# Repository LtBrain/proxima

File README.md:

# proxima
A TVC and fin control flight computer

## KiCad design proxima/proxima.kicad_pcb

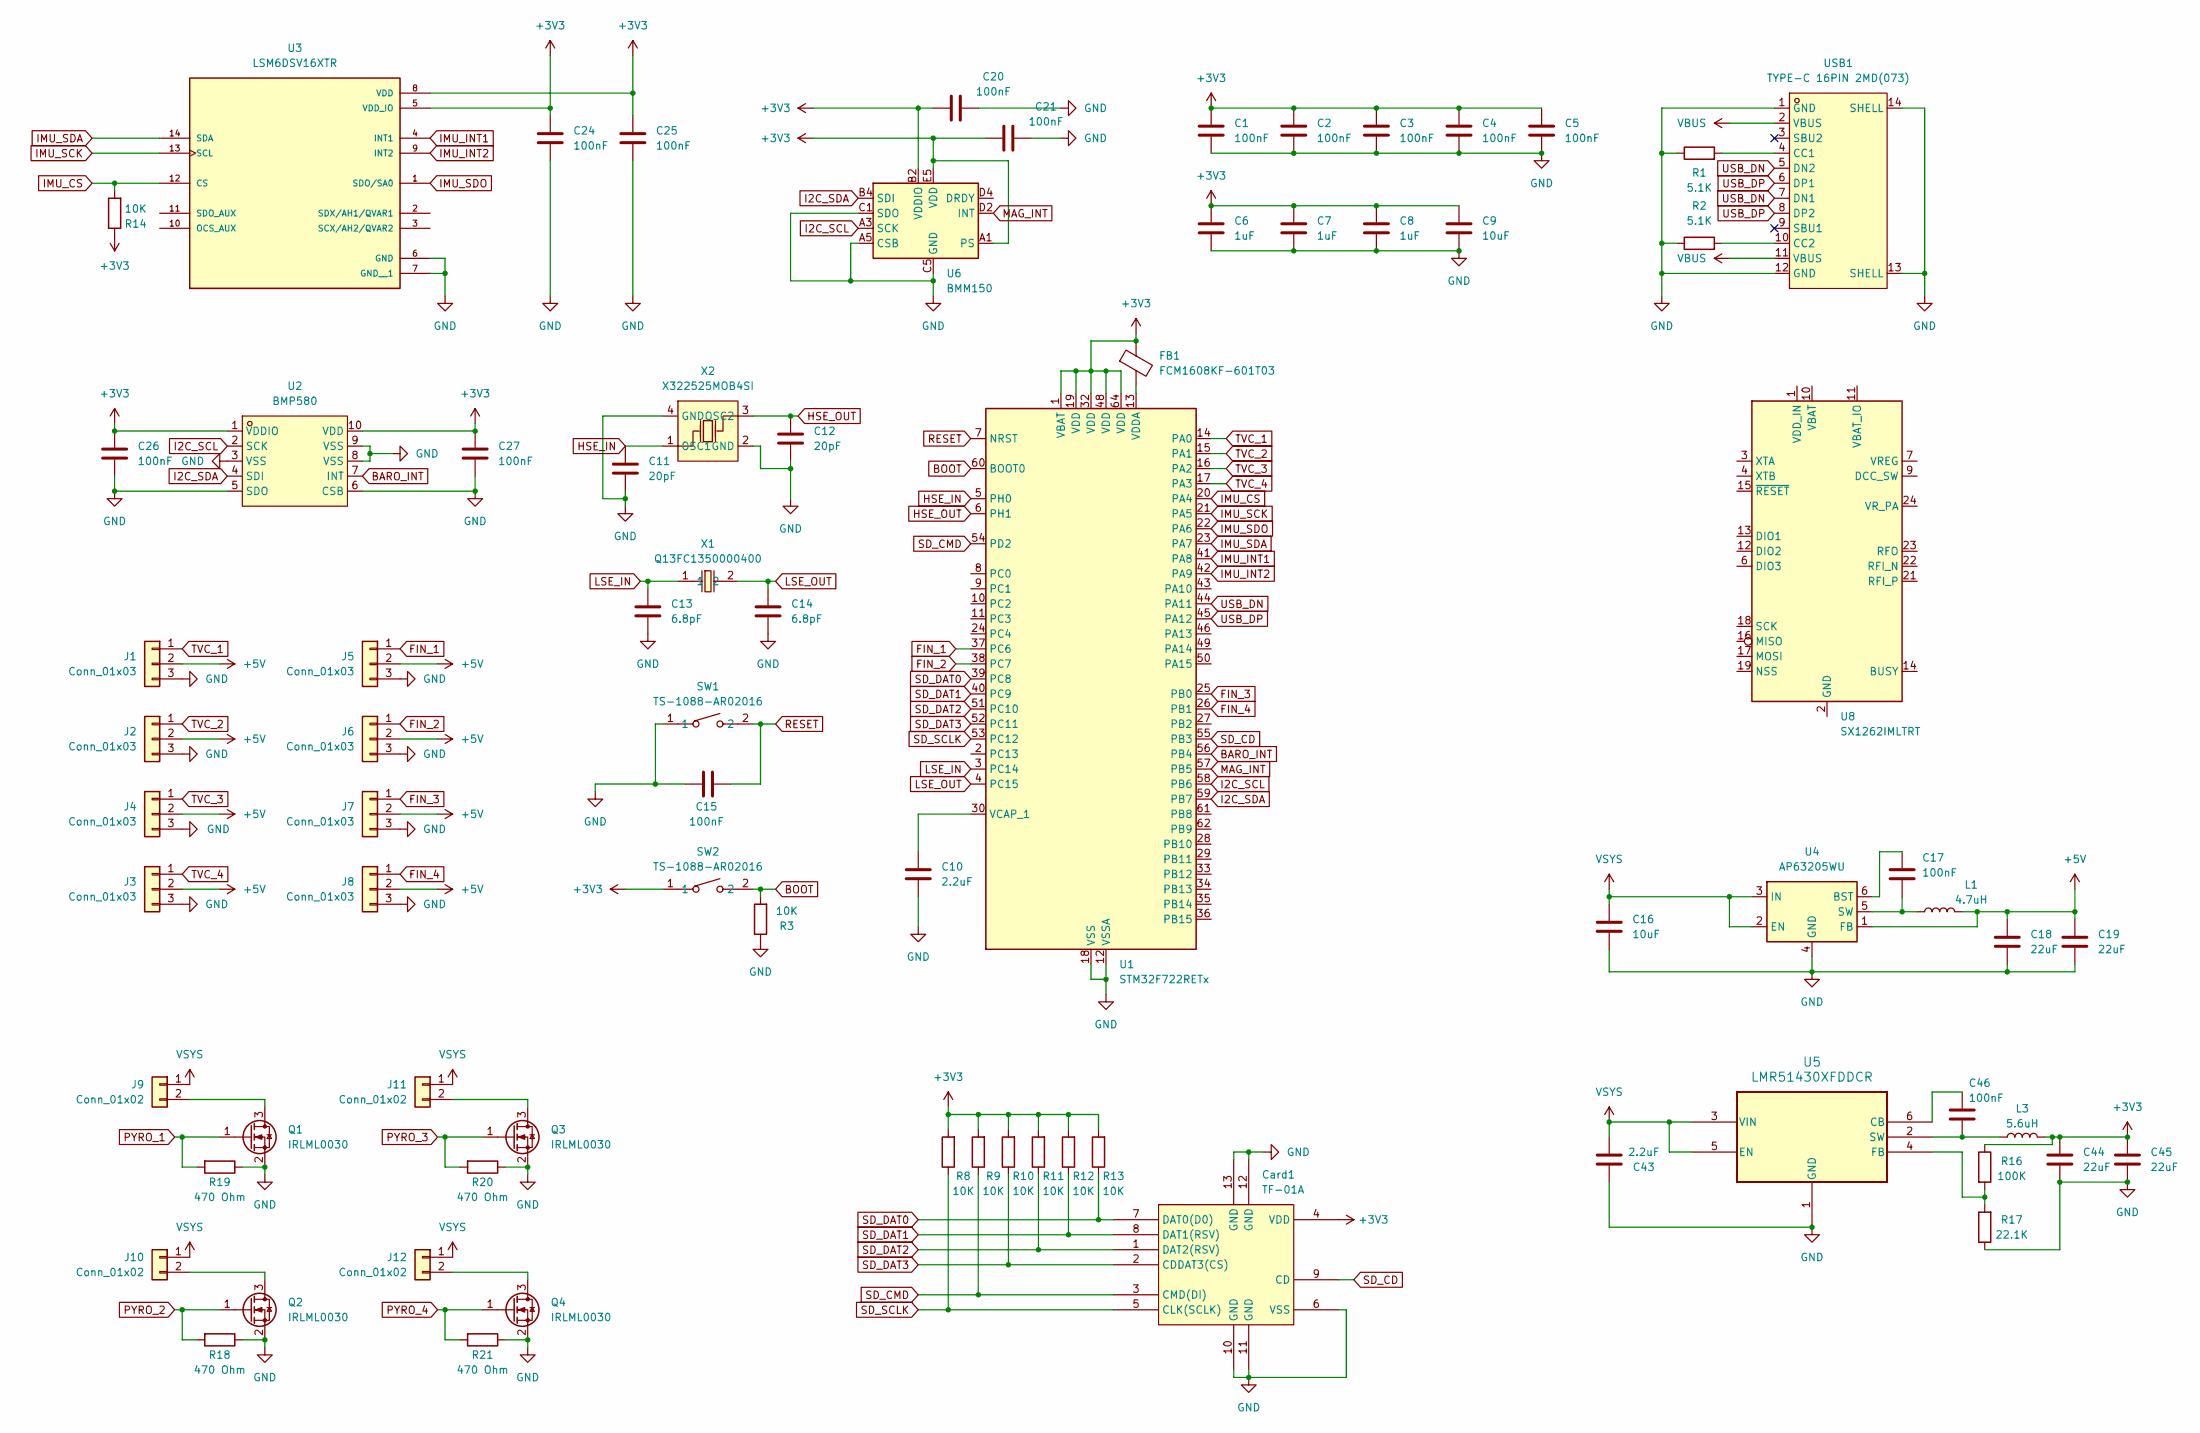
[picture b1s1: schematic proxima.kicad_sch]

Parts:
C1, C2, C3, C4, C5, C15, C17, C20, C21, C24, C25, C26, C27, C46: 100nF; C_0402_1005Metric
C6, C7, C8: 1uF; C_0402_1005Metric
C9: 10uF; C_0402_1005Metric
C10: 2.2uF; C_0402_1005Metric
C11, C12: 20pF; C_0402_1005Metric
C13, C14: 6.8pF; C_0402_1005Metric
C16: 10uF; C_0805_2012Metric
C18, C19, C44, C45: 22uF; C_0805_2012Metric
C43: 2.2uF; C_0805_2012Metric
Card1: TF-01A; TF-SMD_TF-01A; LCSC Part C91145
FB1: FCM1608KF-601T03; L_0603_1608Metric
J1, J2, J3, J4, J5, J6, J7, J8: Conn_01x03; PinHeader_1x03_P2.54mm_Vertical
J9, J10, J11, J12: Conn_01x02; PinHeader_1x02_P2.54mm_Vertical
L1: 4.7uH; L_Coilcraft_XxL4020
L3: 5.6uH; L_Coilcraft_XxL4020
Q1, Q2, Q3, Q4: IRLML0030; SOT-23
R1, R2: 5.1K; R_0402_1005Metric
R3, R8, R9, R10, R11, R12, R13, R14: 10K; R_0402_1005Metric
R16: 100K; R_0402_1005Metric
R17: 22.1K; R_0402_1005Metric
R18, R19, R20, R21: 470 Ohm; R_0402_1005Metric
SW1, SW2: TS-1088-AR02016; SW-SMD_L3.9-W3.0-P4.45; LCSC Part C720477
U1: STM32F722RETx; LQFP-64_10x10mm_P0.5mm
U2: BMP580; LGA-10_L2.0-W2.0-P0.50-TL_BMP580; LCSC Part C22391138
U3: LSM6DSV16XTR; XDCR_LSM6DSV16XTR; PARTREV 4
U4: AP63205WU; TSOT-23-6
U5: LMR51430XFDDCR; SOT-23-THIN-6_DDC_TEX
U6: BMM150; WLCSP-12_1.56x1.56mm_P0.4mm
U8: SX1262IMLTRT; QFN-24-1EP_4x4mm_P0.5mm_EP2.6x2.6mm
USB1: TYPE-C 16PIN 2MD(073); USB-C-SMD_TYPE-C-6PIN-2MD-073; LCSC Part C2765186
X1: Q13FC1350000400; FC-135R_L3.2-W1.5; LCSC Part C32346
X2: X322525MOB4SI; CRYSTAL-SMD_4P-L3.2-W2.5-BL; LCSC Part C9006

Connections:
+3V3: C1.1, C2.1, C3.1, C4.1, C5.1, C6.1, C7.1, C8.1, C9.1, C20.1, C21.1, C24.1, C25.1, C26.1, C27.1, C44.1, C45.1, Card1.4 (VDD), FB1.1, L3.2, R8.2, R9.2, R10.2, R11.2, R12.2, R13.2, R14.1, R16.1, SW2.1, U1.1 (VBAT), U1.19 (VDD), U1.32 (VDD), U1.48 (VDD), U1.64 (VDD), U2.1 (VDDIO), U2.10 (VDD), U3.5 (VDD_IO), U3.8 (VDD), U6.A1 (PS), U6.B2 (VDDIO), U6.E5 (VDD)
+5V: C18.1, C19.1, J1.2, J2.2, J3.2, J4.2, J5.2, J6.2, J7.2, J8.2, L1.2, U4.1 (FB)
BARO_INT: U1.56 (PB4), U2.7 (INT)
BOOT: R3.2, SW2.2, U1.60 (BOOT0)
FIN_1: J5.1, U1.37 (PC6)
FIN_2: J6.1, U1.38 (PC7)
FIN_3: J7.1, U1.25 (PB0)
FIN_4: J8.1, U1.26 (PB1)
GND: C1.2, C2.2, C3.2, C4.2, C5.2, C6.2, C7.2, C8.2, C9.2, C10.2, C11.2, C12.2, C13.2, C14.2, C15.1, C16.2, C18.2, C19.2, C20.2, C21.2, C24.2, C25.2, C26.2, C27.2, C43.1, C44.2, C45.2, Card1.6 (VSS), Card1.10 (GND), Card1.11 (GND), Card1.12 (GND), Card1.13 (GND), J1.3, J2.3, J3.3, J4.3, J5.3, J6.3, J7.3, J8.3, Q1.2 (S), Q2.2 (S), Q3.2 (S), Q4.2 (S), R1.1, R2.1, R3.1, R17.1, R18.1, R19.1, R20.1, R21.1, SW1.1, U1.12 (VSSA), U1.18 (VSS), U1.31 (VSS), U1.47 (VSS), U1.63 (VSS), U2.3 (VSS), U2.5 (SDO), U2.6 (CSB), U2.8 (VSS), U2.9 (VSS), U3.6 (GND), U3.7 (GND__1), U4.4 (GND), U5.1 (GND), U6.A5 (CSB), U6.C1 (SDO), U6.C5 (GND), U6.E1 (GND), U6.E3 (GND), USB1.1 (GND), USB1.12 (GND), USB1.13 (SHELL), USB1.14 (SHELL), X2.2 (GND), X2.4 (GND)
HSE_IN: C11.1, U1.5 (PH0), X2.1 (OSC1)
HSE_OUT: C12.1, U1.6 (PH1), X2.3 (OSC2)
I2C_SCL: U1.58 (PB6), U2.2 (SCK), U6.A3 (SCK)
I2C_SDA: U1.59 (PB7), U2.4 (SDI), U6.B4 (SDI)
IMU_CS: R14.2, U1.20 (PA4), U3.12 (CS)
IMU_INT1: U1.41 (PA8), U3.4 (INT1)
IMU_INT2: U1.42 (PA9), U3.9 (INT2)
IMU_SCK: U1.21 (PA5), U3.13 (SCL)
IMU_SDA: U1.23 (PA7), U3.14 (SDA)
IMU_SDO: U1.22 (PA6), U3.1 (SDO/SA0)
LSE_IN: C13.1, U1.3 (PC14), X1.1
LSE_OUT: C14.1, U1.4 (PC15), X1.2
unnamed: J9.2, Q1.3 (D)
unnamed: J10.2, Q2.3 (D)
unnamed: J11.2, Q3.3 (D)
unnamed: J12.2, Q4.3 (D)
unnamed: C10.1, U1.30 (VCAP_1)
unnamed: FB1.2, U1.13 (VDDA)
unnamed: C17.1, U4.6 (BST)
unnamed: C17.2, L1.1, U4.5 (SW)
unnamed: C46.1, U5.6 (CB)
unnamed: R16.2, R17.2, U5.4 (FB)
unnamed: C46.2, L3.1, U5.2 (SW)
unnamed: U1.57 (PB5), U6.D2 (INT)
unnamed: U8.2 (GND), U8.5 (GND), U8.8 (GND), U8.20 (GND), U8.25 (GND)
unnamed: R1.2, USB1.4 (CC1)
unnamed: R2.2, USB1.10 (CC2)
PYRO_1: Q1.1 (G), R19.2
PYRO_2: Q2.1 (G), R18.2
PYRO_3: Q3.1 (G), R20.2
PYRO_4: Q4.1 (G), R21.2
RESET: C15.2, SW1.2, U1.7 (NRST)
SD_CD: Card1.9 (CD), U1.55 (PB3)
SD_CMD: Card1.3 (CMD(DI)), R9.1, U1.54 (PD2)
SD_DAT0: Card1.7 (DAT0(D0)), R13.1, U1.39 (PC8)
SD_DAT1: Card1.8 (DAT1(RSV)), R12.1, U1.40 (PC9)
SD_DAT2: Card1.1 (DAT2(RSV)), R11.1, U1.51 (PC10)
SD_DAT3: Card1.2 (CDDAT3(CS)), R10.1, U1.52 (PC11)
SD_SCLK: Card1.5 (CLK(SCLK)), R8.1, U1.53 (PC12)
TVC_1: J1.1, U1.14 (PA0)
TVC_2: J2.1, U1.15 (PA1)
TVC_3: J4.1, U1.16 (PA2)
TVC_4: J3.1, U1.17 (PA3)
USB_DN: U1.44 (PA11), USB1.5 (DN2), USB1.7 (DN1)
USB_DP: U1.45 (PA12), USB1.6 (DP1), USB1.8 (DP2)
VBUS: USB1.2 (VBUS), USB1.11 (VBUS)
VSYS: C16.1, C43.2, J9.1, J10.1, J11.1, J12.1, U4.2 (EN), U4.3 (IN), U5.3 (VIN), U5.5 (EN)

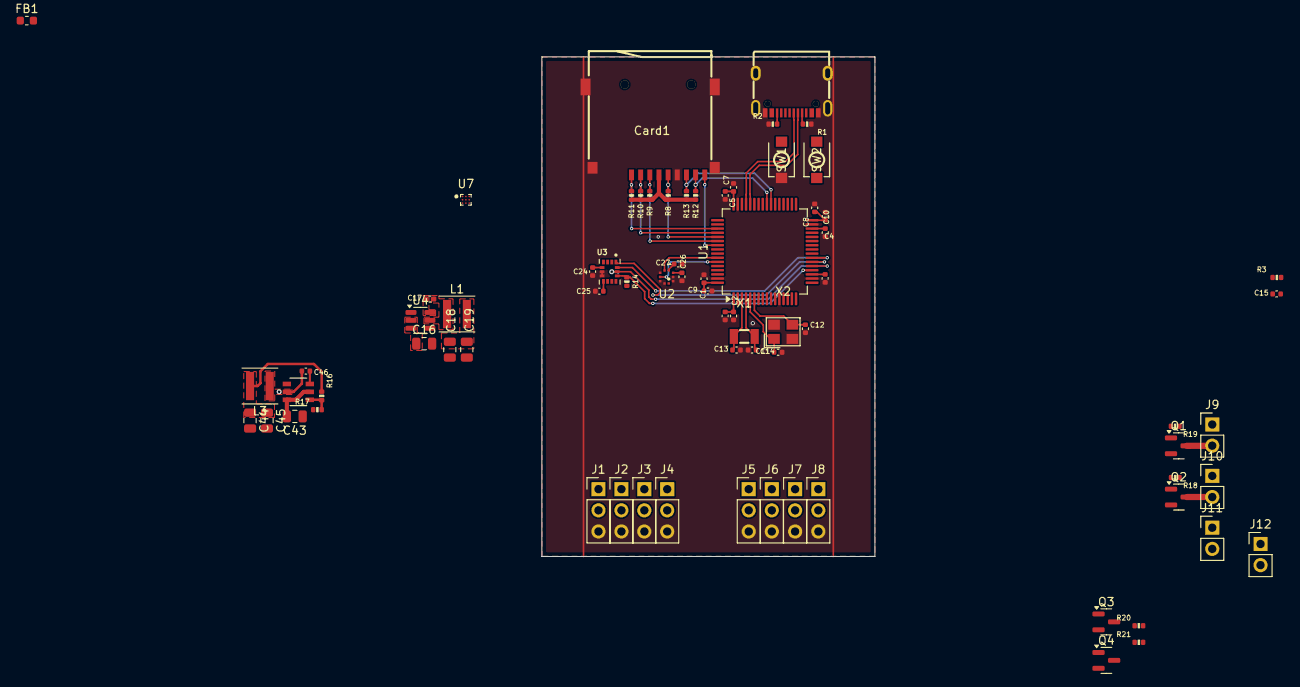
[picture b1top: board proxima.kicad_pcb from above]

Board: 4 copper layers, 40.0 x 60.0 mm, 74 parts (0 on the bottom side), 53 nets.

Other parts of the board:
U7: BMM350; BGA9C40P3X3_128X128X50

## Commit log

2025-11-30 base schematic
2025-11-30 fix github repo?
